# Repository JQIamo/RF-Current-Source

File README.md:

# RF-Current-Source

A wideband radiofrequency voltage-controlled current source designed by D. Barker and A. Restelli.
Our design is released under the CERN Open Hardware License v1.2 and can be cited using .

The eagle files in this repository will be much easier to use with [eagle-config](https://github.com/JQIamo/eagle-config) installed and configured.

For more detailed documentation, go to the [Wiki](https://github.com/JQIamo/RF-Current-Source/wiki/). A detailed write-up of the RF current source's specifications can be found in our paper.

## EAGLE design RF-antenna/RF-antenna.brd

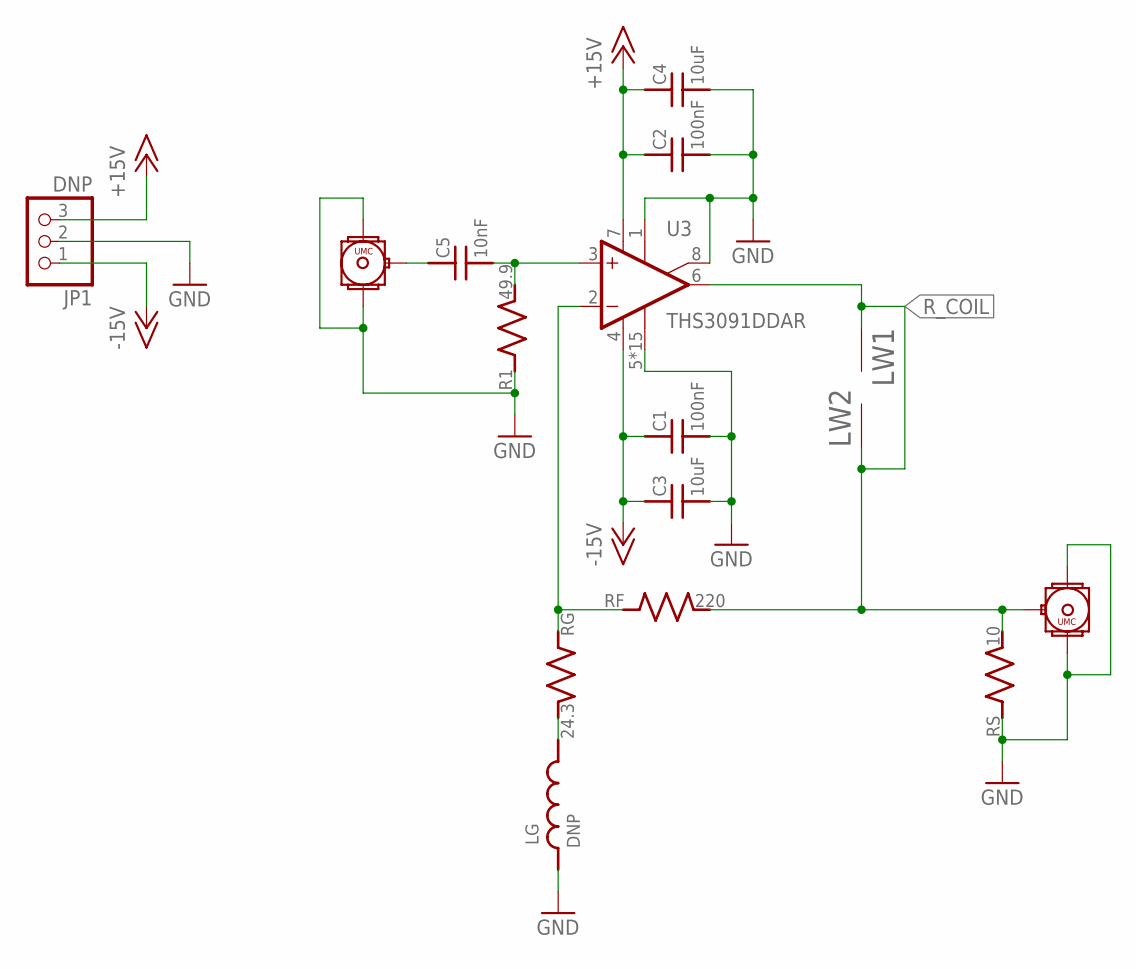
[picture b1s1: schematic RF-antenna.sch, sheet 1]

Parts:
C1, C2: 100nF; C_MLCC_0603; PARTNO 06035C104K4Z2A
C3, C4: 10uF; C_MLCC_1206; PARTNO CL31A106MBHNNNE
C5: 10nF; C_MLCC_0402; PARTNO CL05B103KB5NNNC
CON1, CON2: UMC_CONNECTORREGULAR; UMC_CONNECTOR; PARTNO 1909763-1
JP1: DNP; 1X03; PARTNO 640456-3
LG: DNP; 1008
LW1, LW2: LITZ_TERM; LITZ_100MHZ
R1: 49.9; R_0402; PARTNO ERA-2AEB49R9X
RF: 220; R_0603; PARTNO TNPW0603220RBEEA
RG: 24.3; R_0402; PARTNO RP73PF1E24R3BTD
RS: 10; R_1206; PARTNO PHP01206E10R0BST5
U3: THS3091DDAR; DDA8_2P28X2P28; PARTNO THS3091DDAR

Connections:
+15V: C2.P$1 (1), C4.P$1 (1), JP1.3, U3.7 (V+); also elsewhere on the board
-15V: C1.P$1 (1), C3.P$1 (1), JP1.1, U3.4 (V-); also elsewhere on the board
GND: C1.P$2 (2), C2.P$2 (2), C3.P$2 (2), C4.P$2 (2), CON1.P$2, CON1.P$3, CON2.P$2, CON2.P$3, JP1.2, LG.P$1 (1), R1.P$1 (1), RS.P$1 (1), U3.1 (ON1), U3.5 (OPT), U3.8 (ON2), U3.EPAD (OPT), U3.P$1 (OPT), U3.P$2 (OPT), U3.P$3 (OPT), U3.P$4 (OPT), U3.P$5 (OPT), U3.P$6 (OPT), U3.P$7 (OPT), U3.P$8 (OPT), U3.P$9 (OPT), U3.P$10 (OPT), U3.P$11 (OPT), U3.P$12 (OPT), U3.P$13 (OPT); also elsewhere on the board
unnamed: RF.P$1 (1), RG.P$1 (1), U3.2 (-IN)
unnamed: C5.P$2 (2), R1.P$2 (2), U3.3 (+IN)
unnamed: C5.P$1 (1), CON2.P$1
unnamed: LG.P$2 (2), RG.P$2 (2)
R_COIL: CON1.P$1, LW1.T1, LW2.T1, RF.P$2 (2), RS.P$2 (2), U3.6 (OUT)

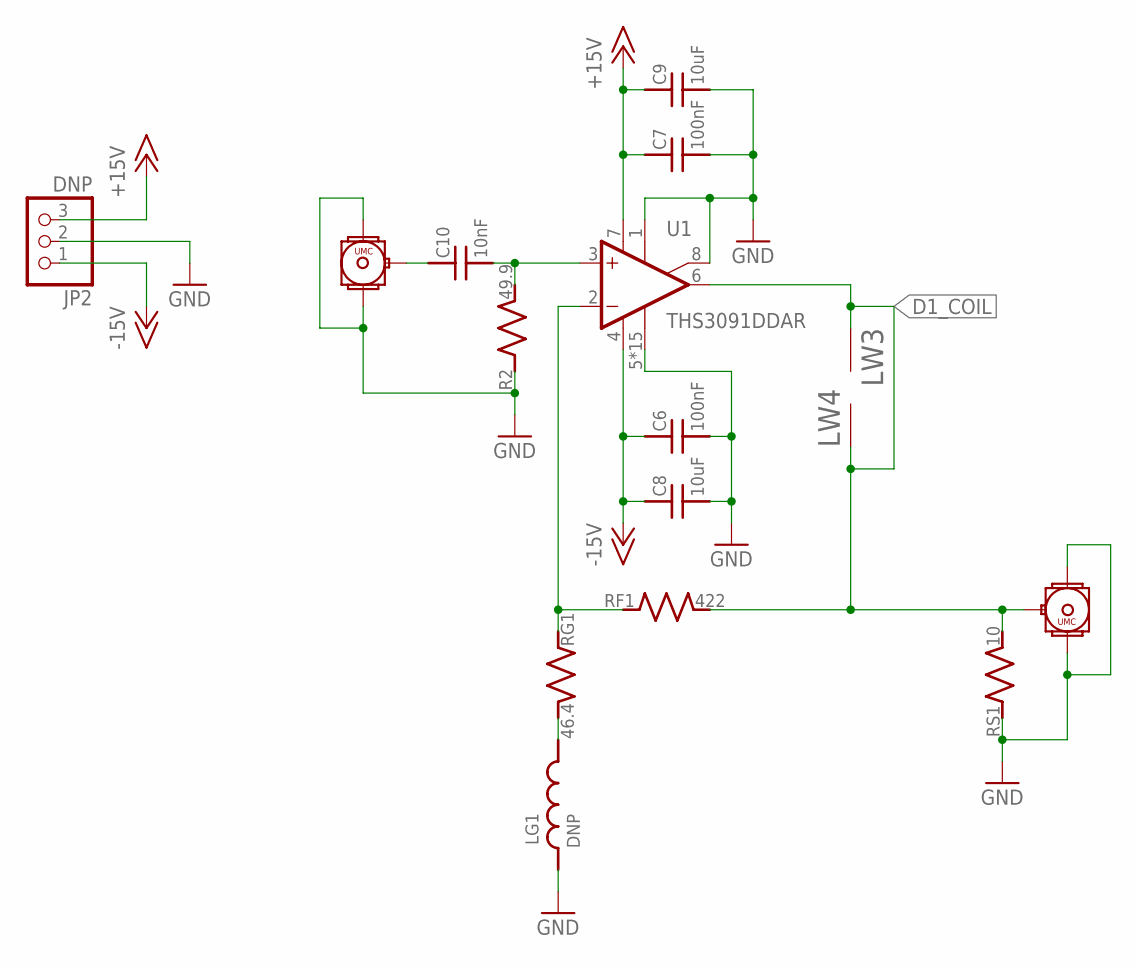
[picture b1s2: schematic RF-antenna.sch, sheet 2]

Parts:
C6, C7: 100nF; C_MLCC_0603; PARTNO 06035C104K4Z2A
C8, C9: 10uF; C_MLCC_1206; PARTNO CL31A106MBHNNNE
C10: 10nF; C_MLCC_0402; PARTNO CL05B103KB5NNNC
CON3, CON4: UMC_CONNECTORREGULAR; UMC_CONNECTOR; PARTNO 1909763-1
JP2: DNP; 1X03; PARTNO 640456-3
LG1: DNP; 1008
LW3, LW4: LITZ_TERM; LITZ_100MHZ
R2: 49.9; R_0402; PARTNO ERA-2AEB49R9X
RF1: 422; R_0603; PARTNO TNPW0603422RBEEA
RG1: 46.4; R_0402; PARTNO RP73PF1E46R4BTD
RS1: 10; R_1206; PARTNO PHP01206E10R0BST5
U1: THS3091DDAR; DDA8_2P28X2P28; PARTNO THS3091DDAR

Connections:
+15V: C7.P$1 (1), C9.P$1 (1), JP2.3, U1.7 (V+); also elsewhere on the board
-15V: C6.P$1 (1), C8.P$1 (1), JP2.1, U1.4 (V-); also elsewhere on the board
D1_COIL: CON4.P$1, LW3.T1, LW4.T1, RF1.P$2 (2), RS1.P$2 (2), U1.6 (OUT)
GND: C6.P$2 (2), C7.P$2 (2), C8.P$2 (2), C9.P$2 (2), CON3.P$2, CON3.P$3, CON4.P$2, CON4.P$3, JP2.2, LG1.P$1 (1), R2.P$1 (1), RS1.P$1 (1), U1.1 (ON1), U1.5 (OPT), U1.8 (ON2), U1.EPAD (OPT), U1.P$1 (OPT), U1.P$2 (OPT), U1.P$3 (OPT), U1.P$4 (OPT), U1.P$5 (OPT), U1.P$6 (OPT), U1.P$7 (OPT), U1.P$8 (OPT), U1.P$9 (OPT), U1.P$10 (OPT), U1.P$11 (OPT), U1.P$12 (OPT), U1.P$13 (OPT); also elsewhere on the board
unnamed: RF1.P$1 (1), RG1.P$1 (1), U1.2 (-IN)
unnamed: C10.P$2 (2), R2.P$2 (2), U1.3 (+IN)
unnamed: C10.P$1 (1), CON3.P$1
unnamed: LG1.P$2 (2), RG1.P$2 (2)

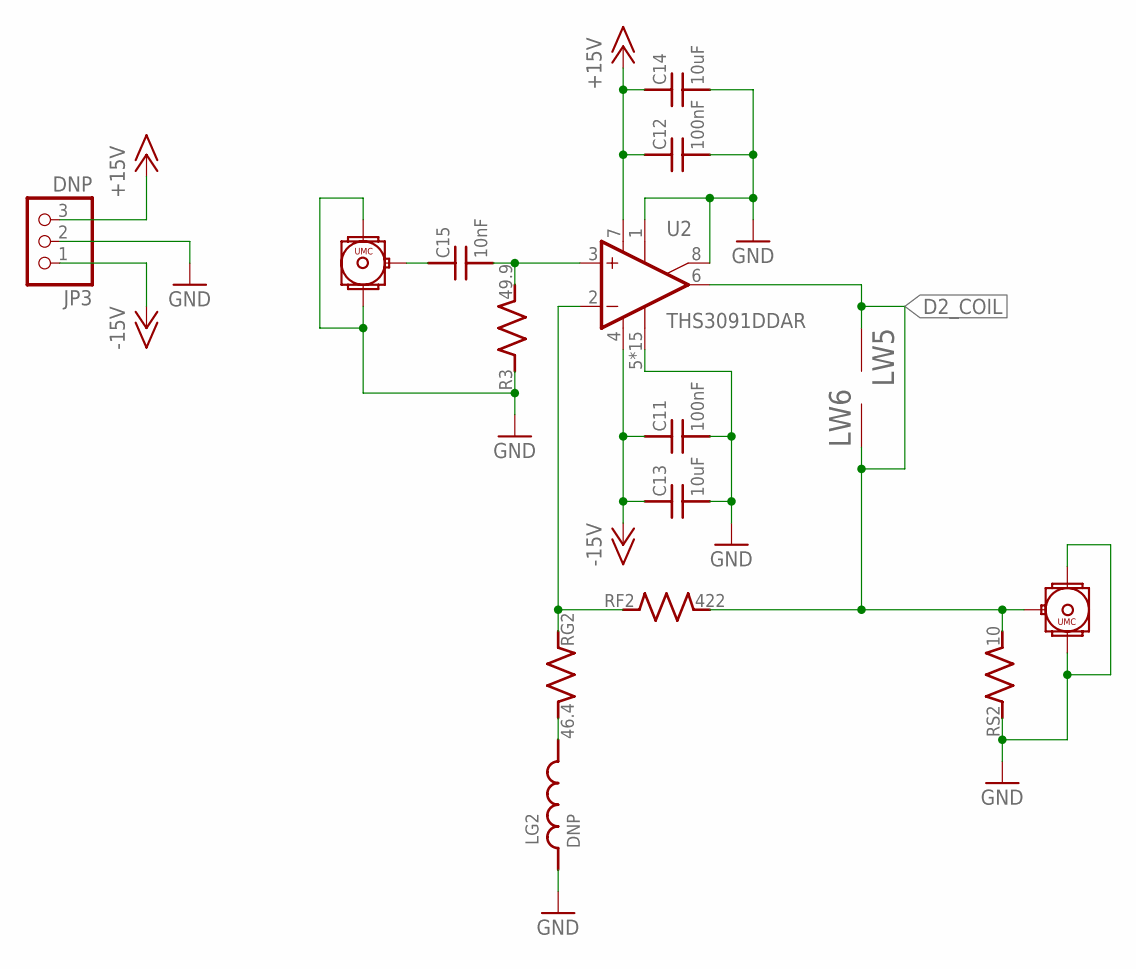
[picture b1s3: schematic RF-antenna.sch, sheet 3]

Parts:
C11, C12: 100nF; C_MLCC_0603; PARTNO 06035C104K4Z2A
C13, C14: 10uF; C_MLCC_1206; PARTNO CL31A106MBHNNNE
C15: 10nF; C_MLCC_0402; PARTNO CL05B103KB5NNNC
CON5, CON6: UMC_CONNECTORREGULAR; UMC_CONNECTOR; PARTNO 1909763-1
JP3: DNP; 1X03; PARTNO 640456-3
LG2: DNP; 1008
LW5, LW6: LITZ_TERM; LITZ_100MHZ
R3: 49.9; R_0402; PARTNO ERA-2AEB49R9X
RF2: 422; R_0603; PARTNO TNPW0603422RBEEA
RG2: 46.4; R_0402; PARTNO RP73PF1E46R4BTD
RS2: 10; R_1206; PARTNO PHP01206E10R0BST5
U2: THS3091DDAR; DDA8_2P28X2P28; PARTNO THS3091DDAR

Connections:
+15V: C12.P$1 (1), C14.P$1 (1), JP3.3, U2.7 (V+); also elsewhere on the board
-15V: C11.P$1 (1), C13.P$1 (1), JP3.1, U2.4 (V-); also elsewhere on the board
D2_COIL: CON6.P$1, LW5.T1, LW6.T1, RF2.P$2 (2), RS2.P$2 (2), U2.6 (OUT)
GND: C11.P$2 (2), C12.P$2 (2), C13.P$2 (2), C14.P$2 (2), CON5.P$2, CON5.P$3, CON6.P$2, CON6.P$3, JP3.2, LG2.P$1 (1), R3.P$1 (1), RS2.P$1 (1), U2.1 (ON1), U2.5 (OPT), U2.8 (ON2), U2.EPAD (OPT), U2.P$1 (OPT), U2.P$2 (OPT), U2.P$3 (OPT), U2.P$4 (OPT), U2.P$5 (OPT), U2.P$6 (OPT), U2.P$7 (OPT), U2.P$8 (OPT), U2.P$9 (OPT), U2.P$10 (OPT), U2.P$11 (OPT), U2.P$12 (OPT), U2.P$13 (OPT); also elsewhere on the board
unnamed: RF2.P$1 (1), RG2.P$1 (1), U2.2 (-IN)
unnamed: C15.P$2 (2), R3.P$2 (2), U2.3 (+IN)
unnamed: C15.P$1 (1), CON5.P$1
unnamed: LG2.P$2 (2), RG2.P$2 (2)

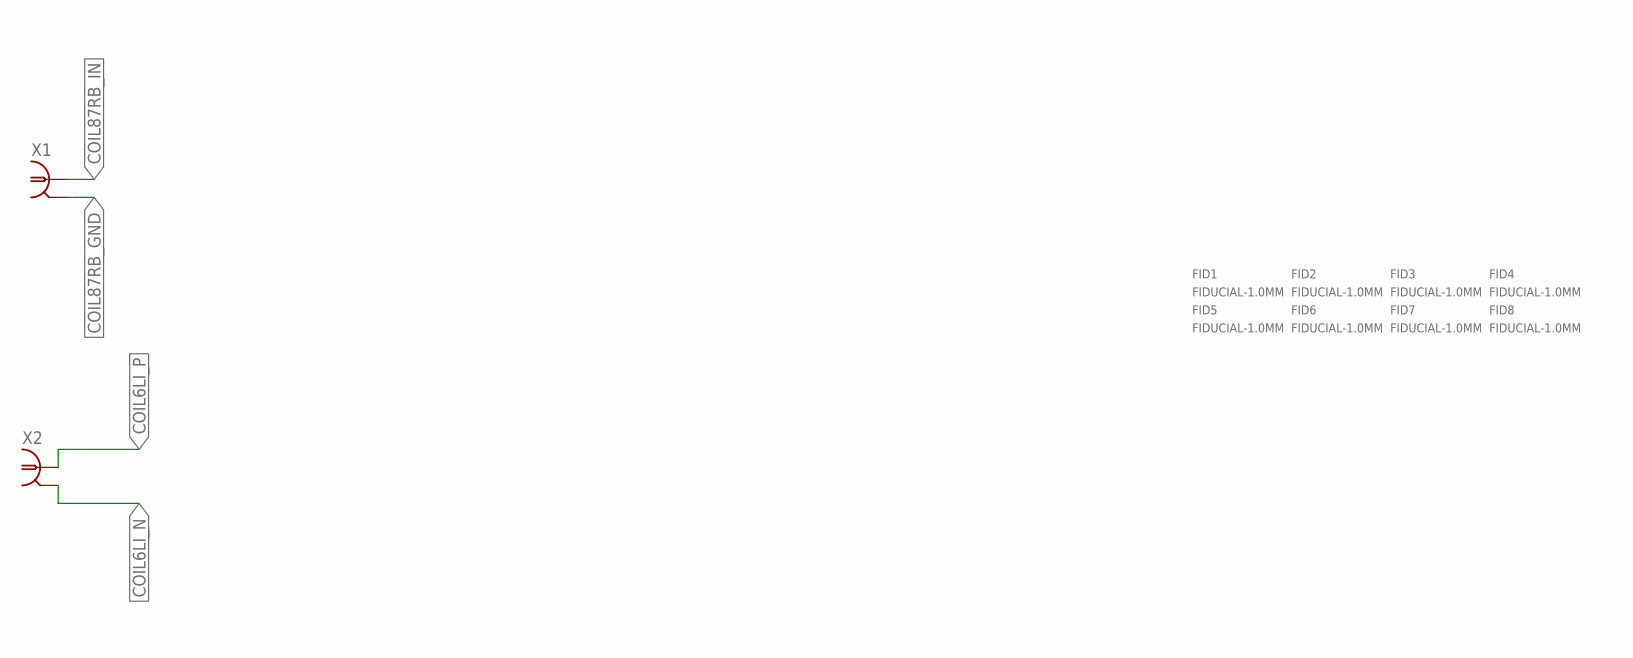
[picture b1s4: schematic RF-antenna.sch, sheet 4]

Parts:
FID1, FID2, FID3, FID4, FID5, FID6, FID7, FID8: FIDUCIAL-1.0MM; FID_1.0MM
X1, X2: SMA-V; PARTNO 5-1814832-1

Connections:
COIL6LI_N: X2.GND1 (2), X2.GND2 (2), X2.GND3 (2), X2.GND4 (2)
COIL6LI_P: X2.RF (1)
COIL87RB_GND: X1.GND1 (2), X1.GND2 (2), X1.GND3 (2), X1.GND4 (2)
COIL87RB_IN: X1.RF (1)

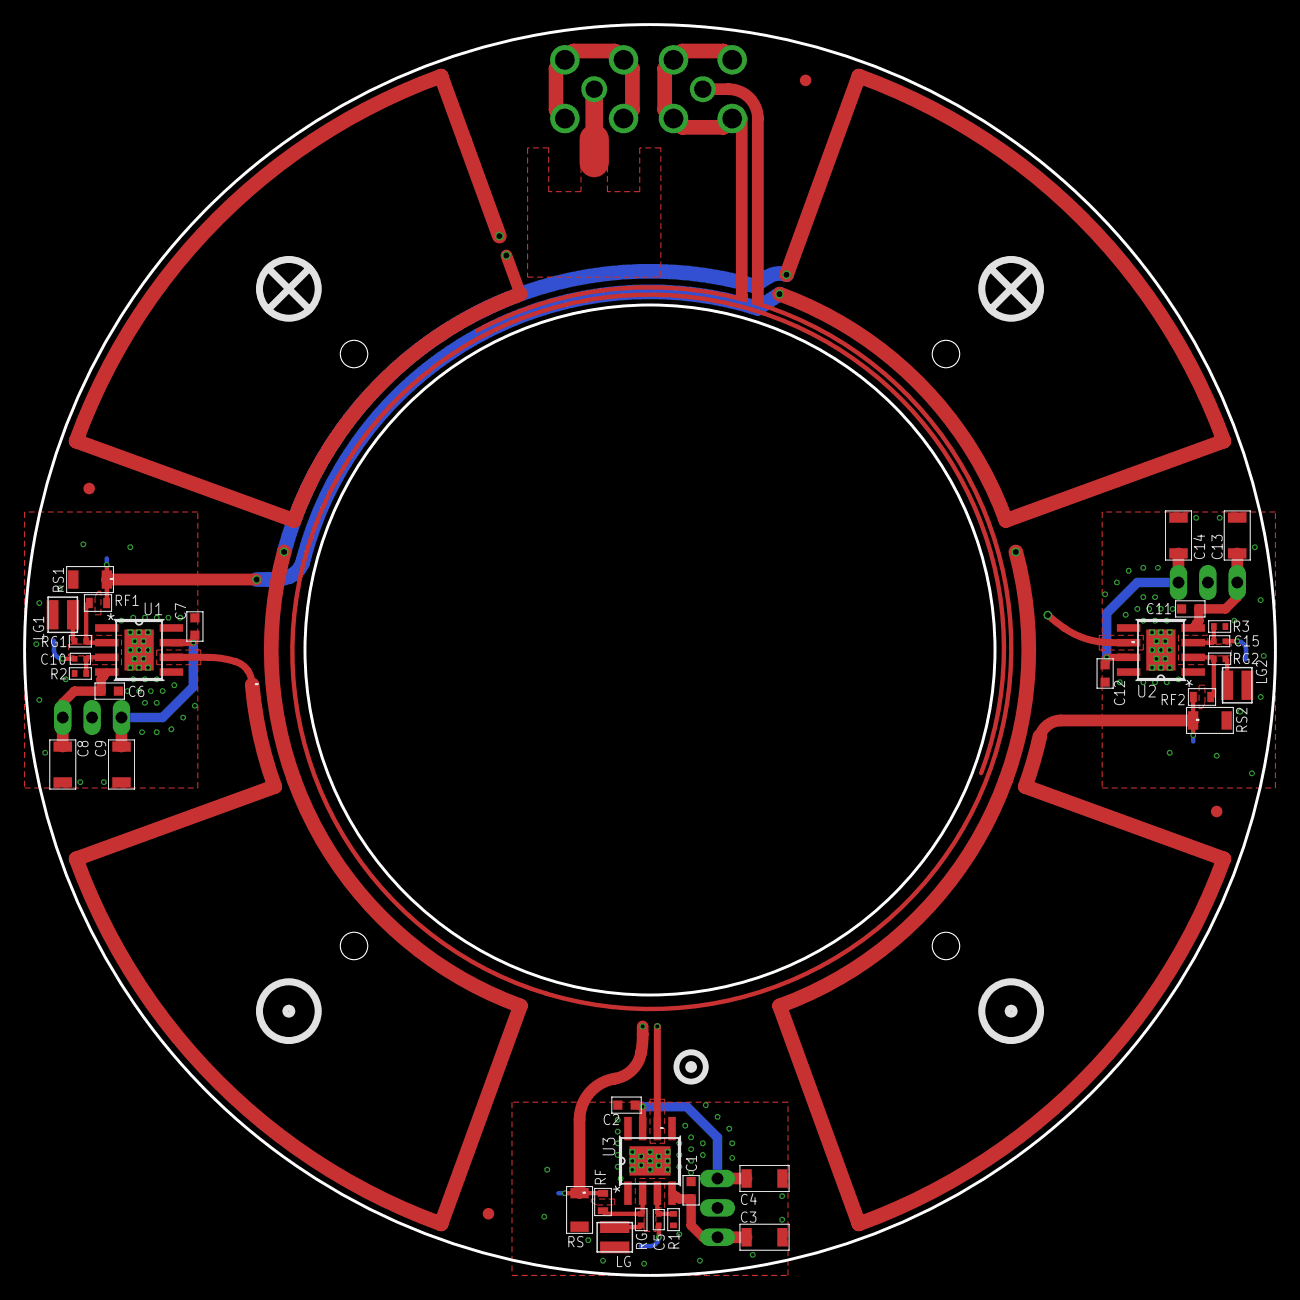
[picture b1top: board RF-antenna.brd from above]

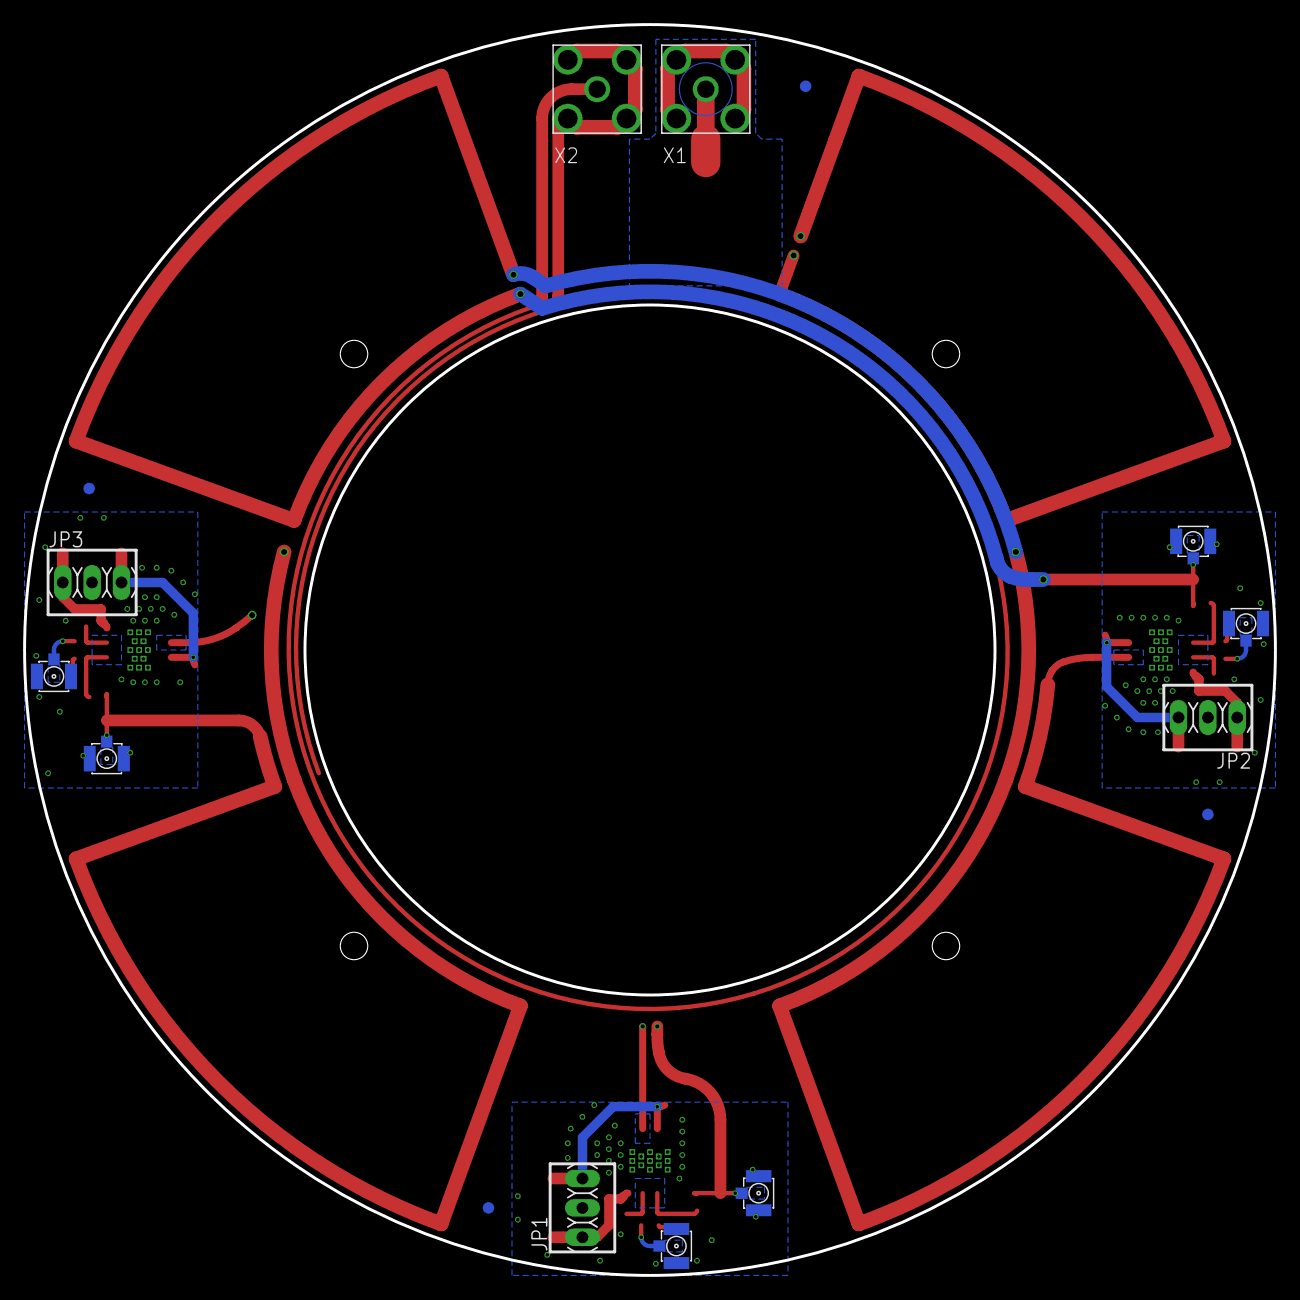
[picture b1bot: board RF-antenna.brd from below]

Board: 4 copper layers, 108.2 x 108.2 mm, 58 parts (15 on the bottom side), 20 nets.

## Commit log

2018-03-02 :space_invader: Added .gitattributes & .gitignore files
2018-03-02 Initial Commit
    Pushing antenna files to git.
    DSB
2018-03-20 Adding parts for footprinting
    Added a bunch of test components to get an idea of how tight the design
    will be. Also corrected the keepout areas.
    DSB
2018-03-21 More footprints
    Added a few more component footprints to see what is up and test layout.
    DSB
2018-05-25 add library
    Adding a library for design of Litz wire.
    DSB
2018-06-04 Quick Push
    Added buffers and minimal schematic.
    DSB
2018-06-07 Zeroth order design
    Quick layout for testing with Alessandro.
    DSB
2018-08-24 Starting full board layout
    Got the VtoI converter designed and have started laying out the RF antennas.
    DSB
2018-08-27 Finished 1st order prototype
    Ready to discuss with Alessandro and Steve. Rough estimate that one board will generate 20 kHz Rabi frequencies with the circular coil.
    DSB
2018-08-29 Qucs simulation
    Pushing the qucs simulation of the RF V to I converter.
    DSB
2018-08-30 Fix antenna polarity
    The polarity of half of each of the D-shaped antennas was incorrect. I've adjusted so that the D antennas produce B fields pointing along the diagonal as desired.
    DSB
2018-10-18 Test board ready
    Pushing the prepared test board complete with 230 MHz and 6.8 GHz antennas for hyperfine control.
    DSB
2018-10-18 git lfs test
    Trying to push a COMSOL file with git lfs.
    DSB
2018-10-18 Success
    Got COMSOL to push, now updating with additional COMSOL and files for Macrofab.
    DSB
2018-10-19 85Rb antenna
    Adding the patch antenna design for 85Rb.
    DSB
2018-12-21 Antenna B
    Added 7Li and 85Rb HF antennas. Also switched polarity of loop antenna.
    DSB
2018-12-21 MacroFab files
    Uploading Macrofab files for antenna B.
    DSB
2019-01-31 Initial loop data
    I placed 560 nH for Lg, 422 Ohm for Rf, 47 Ohm for Rg. The loop antenna has a flat response out to about 40 MHz and the parasitic capacitor resonance is out at about 100 MHz. I should be able to do m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
    DSB
2019-02-05 D coil data
    Can push loop coil out to 50 MHz with some stability cost. The D coil looks like it has the same inductance, so...
    DSB
2019-02-12 More Data
    More data on the RF antennas. Need to move out to NIST to check thermal instability issues on the Bitter coil.
    DSB
2019-02-13 Data on the Bitter coil
    Adding data taken at NIST with the antenna attached to the Bitter coil.
    DSB
2019-02-19 Improving microwaves
    Working to improve the microwave modeling. Looks like I was using the wrong value for Er at high frequency.
    DSB
2019-02-22 Updating microwave antenna sims
    Updating the microwave antenna simulations to reflect the actual high frequency performance of MacroFab's FR4.
    DSB
2019-02-27 Er fitting
    Pushing initial attempt at fitting the permittivity of FR4.
    DSB
2019-03-06 Finished Er fitting
    Fit the data for Er of MacroFab FR4. The Debye model isn't a great fit, but it's kind of close. Need to simulate antennas to cross-check.
    DSB
2019-04-08 Push updated antennas
    Pushing the adjusted antenna designs to model on a faster computer.
    DSB
2019-04-09 New Rb87 Antenna
    Pushing the redesigned Rb87 antenna.
    DSB
2019-04-11 New 6Li antenna
    Finished a spiral dipole design for the 6Li antenna. Testing indicates that it should be okay for Er > 3.8 (the low end of the FR4 spec). Note that the bitter coils presence changes the resonance and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
    DSB
2019-04-15 New 87Rb and 6Li antennas
    I updated the eagle files with the new 87Rb and 6Li antenna designs from COMSOL.
    DSB
2019-04-15 New BOM
    Pushing a new BOM for the RF-antenna PCB.
    DSB
2019-04-15 Updated values
    Changed values in BOM to reflect results from prototype antennas.
    DSB
2019-05-10 Remove microwave antennas
    Removing microwave antennas due to Git LFS limits.
    DSB
2020-02-25 Power amp comparison
    Adding simulation of the RF antenna with a power amplifier.
    DSB
2020-02-25 Create LICENSE
    Adding the CERN OHL.
    DSB
2020-02-25 Figs for wiki
    Pushing a couple figures for the wiki.
    DSB
2020-03-13 More simulations
    Pushing new simulations for phase margin and gain margin.
    DSB
2020-03-13 Added new measurements with 120nH inductor in Data folder
2020-03-23 Push analysis of full transfer Fn
    Tried to find poles and zeros of the full transfer function. It's a mess.
    DSB
2020-04-08 Updated simulations
    Added parameter sweeps to better fit the loop inductance and corrected the circuit for the prescence of the spectrum analyzer.
    DSB
2020-04-08 Transimpedance Simulation
    Adding simulation to estimate the transimpedance of the CFA.
    DSB
2020-04-11 add Ri
    Adding effect of Ri to the transfer function.
    DSB
2020-04-20 Update wiki figures
    Update the figures for the wiki to reflect the most recent data analysis.
    DSB
2020-04-20 Equation
    Push equation for the wiki.
    DSB
2020-04-20 Qucs files
    Pushing most recent version of qucs aux files.
    DSB
2020-07-13 Update transfer Fn
    Updating the mathematica notebook to get a better handle on the transfer function.
    DSB
2020-07-13 More transfer Fn testing
    Pushing some further attempts to factor the transfer function.
    DSB
2020-07-15 Finished notebook updates
    Full transfer function is now figured out. We just need to adjust it into a more readable form.
    DSB
2020-07-17 Updated simulations
    Pushing the most recent transient simulation code. New data is not included (file too large), so simulations will have to be rerun.
    DSB
2020-07-29 Open loop transfer function
    Updating the mathematica notebook with corrected open-loop transfer function.
    DSB
2020-08-17 Update Docs
    Adding new simulation results and transfer function derivation.
    DSB
2020-08-18 Update simulations
    Pushing most recent transient simulation versions of qucs files.
    DSB
2021-11-04 Push new notebooks
    Pushing the new mathematica simulations of the RF antennas.
    DSB
2021-11-24 Push new antenna calculations
    Pushing design for transverse RF antennas.
    DSB

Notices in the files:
README.md:
Our design is released under the CERN Open Hardware License v1.2 and can be cited using [](https://doi.org/10.5281/zenodo.3758488).
